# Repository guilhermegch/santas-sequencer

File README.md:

# Santa's Sequencer
Project for PCB Badge challenge, organized by the Brazilian Computer Engineer and Youtuber Julia (@juliallabs), from the channel "Laboratório da Julia"(Julia's Lab).

My project idea is to make a simple ornament. Its implementation is made with a Johnson decade counter IC, the CD4017, to create a sequencer. The clock circuitry was made by transistors, creating an Astable Multivibrator.

To a more complete info about the design, circuit calculations and how it works, check the documentation pdf file.

On images folder, there's the original .svg draws and the .dxf files, accepted by the Kicad software.

This hardware was developed using Kicad 5.1.8 for Linux.
This hardware is free to use, change, and distribute.

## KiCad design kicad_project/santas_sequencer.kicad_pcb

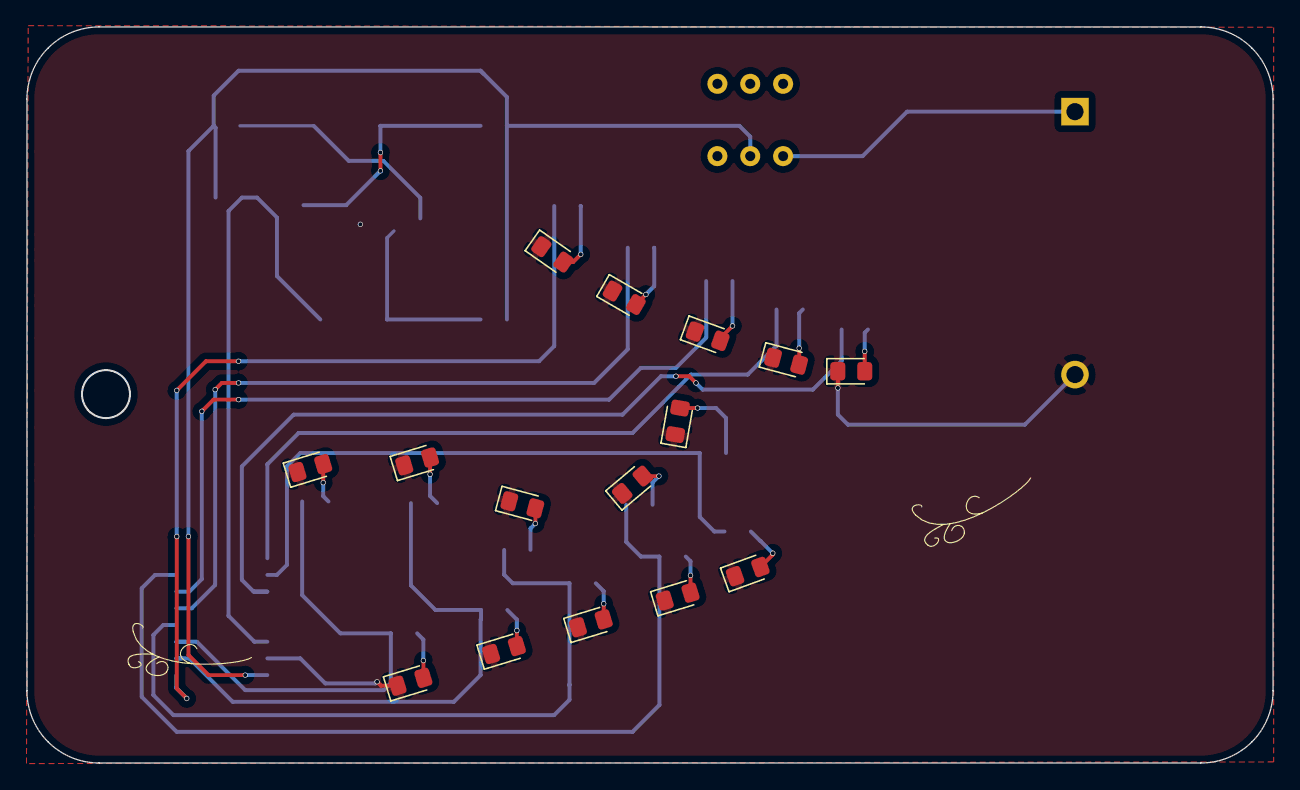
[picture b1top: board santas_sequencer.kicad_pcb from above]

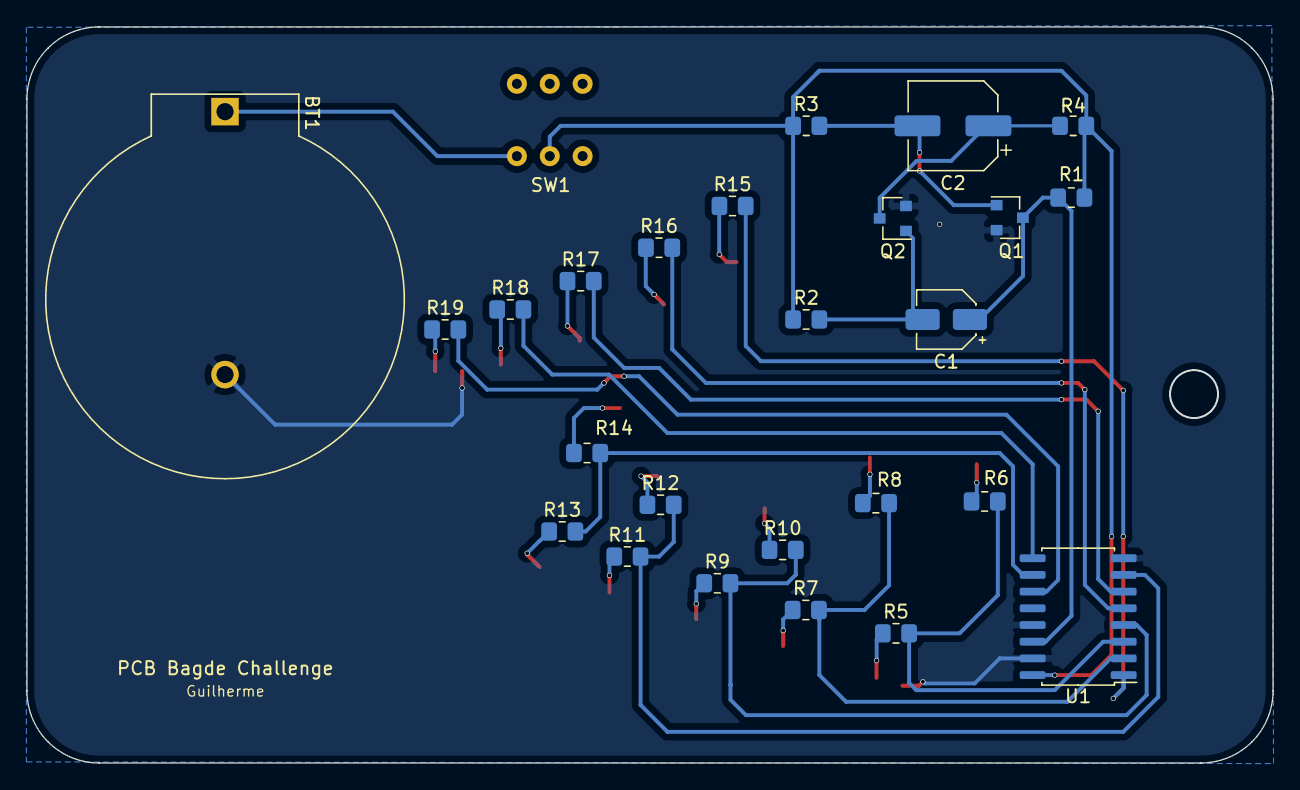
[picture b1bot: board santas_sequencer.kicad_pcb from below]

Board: 2 copper layers, 94.8 x 56.0 mm, 41 parts (26 on the bottom side), 32 nets.

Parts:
BT1: Battery_Cell; BatteryHolder_ComfortableElectronic_CH273-2450_1x2450
C1: 10uF; CP_Elec_4x5.8
C2: 47uF; CP_Elec_6.3x7.7
D1, D2, D3, D4, D5, D6, D7, D8, D9, D10: Red; LED_0805_2012Metric_Pad1.15x1.40mm_HandSolder
D11, D12, D13, D14, D15: White; LED_0805_2012Metric_Pad1.15x1.40mm_HandSolder
Q1, Q2: BC847; SOT-23
R1, R4: 330; R_0805_2012Metric_Pad1.20x1.40mm_HandSolder
R2: 47k; R_0805_2012Metric_Pad1.20x1.40mm_HandSolder
R3: 22k; R_0805_2012Metric_Pad1.20x1.40mm_HandSolder
R5, R6, R7, R8, R9, R10, R11, R12, R13, R14, R15, R16, R17, R18, R19: 100; R_0805_2012Metric_Pad1.20x1.40mm_HandSolder
SW1: SW_DPDT_x2; DPDT_Switch_6_terminals
U1: CD4017; SO-16_5.3x10.2mm_P1.27mm

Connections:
+BATT: R1.1, R2.1, R3.1, R4.1, SW1.3, U1.16
GND: BT1.2, D1.1, D2.1, D3.1, D4.1, D5.1, D6.1, D7.1, D8.1, D9.1, D10.1, D11.1, D12.1, D13.1, D14.1, D15.1, Q1.2, Q2.2, U1.8, U1.13, U1.15
unnamed: BT1.1, SW1.2
unnamed: C1.2, Q2.1, R2.2
unnamed: C2.1, Q2.3, R4.2
unnamed: C2.2, Q1.1, R3.2
unnamed: D1.2, R5.1
unnamed: D2.2, R6.1
unnamed: D3.2, R7.1
unnamed: D4.2, R8.1
unnamed: D5.2, R9.1
unnamed: D6.2, R10.1
unnamed: D7.2, R11.1
unnamed: D8.2, R12.1
unnamed: D9.2, R13.1
unnamed: D10.2, R14.1
unnamed: D11.2, R15.1
unnamed: D12.2, R16.1
unnamed: D13.2, R17.1
unnamed: D14.2, R18.1
unnamed: D15.2, R19.1
unnamed: R5.2, R6.2, U1.3
unnamed: R7.2, R8.2, U1.2
unnamed: R9.2, R10.2, U1.4
unnamed: R11.2, R12.2, U1.7
unnamed: R13.2, R14.2, U1.10
unnamed: R15.2, U1.1
unnamed: R16.2, U1.5
unnamed: R17.2, U1.6
unnamed: R18.2, U1.9
unnamed: R19.2, U1.11
clock: C1.1, Q1.3, R1.2, U1.14

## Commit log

2020-11-27 Add files via upload
    gerber files
2020-11-27 project images
2020-11-27 kicad project files
2020-11-27 BOM list
2020-11-27 project documentation
2020-11-27 project schematic
2020-11-27 project readme
2020-11-27 Removing gerber zip
2020-11-27 gerber zip file
2021-01-27 Updating the pcb to correct a project flaw: the transistors ground plane was isolated from other grounds
